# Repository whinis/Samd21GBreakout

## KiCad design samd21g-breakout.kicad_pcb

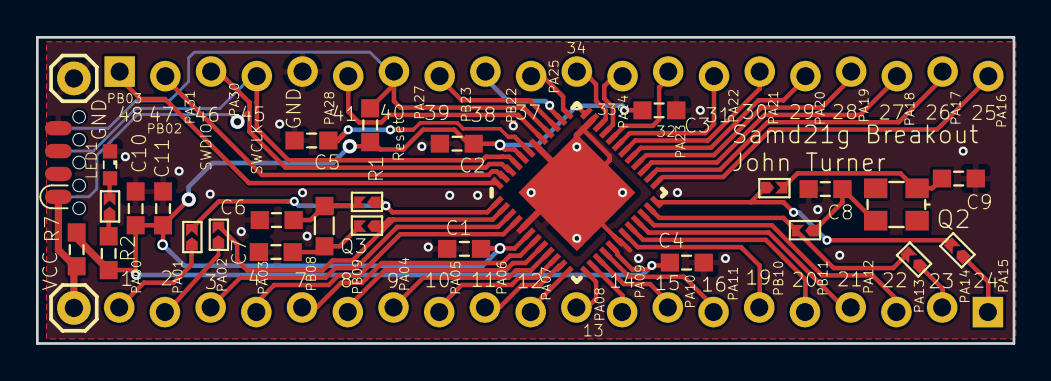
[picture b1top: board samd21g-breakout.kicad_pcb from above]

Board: 2 copper layers, 54.3 x 17.0 mm, 32 parts (0 on the bottom side), 53 nets.

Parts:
C1, C2, C3, C4: 1nf; 0603
C5: 1uf; 0603
C6, C7, C8, C9: CAPACITOR; 0603
C10: 10nf; 0603
C11: 100nf; 0603
J1, J2: CONN_20; PinHeader_1x20_P2.54mm_Vertical_stagger
J3: Conn_02x04_Odd_Even; SOIC_clipProgSmall
J5, J6: CONN_01; 1X01
JP1, JP2, JP3, JP4, JP5, JP6, JP7, JP8, JP9: Jumper_2_Open; SolderJumper-2_P0.6mm_Open_TrianglePad1.0x1.5mm
LED1: LEDSML0603; SML0603
Q2: 48mhz; 3.2X2.5_KX-7
Q3: CRYSTAL3.2X1.5; 3.2X1.5
R1: 10k; 0603
R2, R7: 68; 0603
U$1: ATSAMD21G17A; QFN48

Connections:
/GND: C1.2, C2.2, C3.2, C4.2, C5.2, C6.1, C7.2, C8.1, C9.2, C10.2, C11.2, J2.5, J3.7, J6.1, LED1.C, U$1.5, U$1.18, U$1.35, U$1.42, U$1.EP
/RESET: J2.7, J3.8, R1.1, U$1.40
/SWCLK: J2.4, J3.6, U$1.45
/SWDIO: J2.3, J3.2, U$1.46
/VCC: C1.1, C2.1, C3.1, C4.1, C10.1, C11.1, R1.2, R2.1, R7.2, U$1.6, U$1.17, U$1.36, U$1.44
/VCC_RAW: J3.1, J5.1, R7.1
/VDDCORE: C5.1, U$1.43
unnamed: C6.2, JP5.2, Q3.2
unnamed: C7.1, JP6.2, Q3.1
unnamed: C8.2, JP7.1, Q2.3
unnamed: C9.1, JP8.2, Q2.1
unnamed: J1.1, JP4.1
unnamed: J1.2, JP3.1
unnamed: J1.3, U$1.22
unnamed: J1.4, U$1.21
unnamed: J1.5, U$1.20
unnamed: J1.6, U$1.19
unnamed: J1.7, U$1.16
unnamed: J1.8, U$1.15
unnamed: J1.9, U$1.14
unnamed: J1.10, U$1.13
unnamed: J1.11, U$1.12
unnamed: J1.12, U$1.11
unnamed: J1.13, U$1.10
unnamed: J1.14, U$1.9
unnamed: J1.15, U$1.8
unnamed: J1.16, U$1.7
unnamed: J1.17, U$1.4
unnamed: J1.18, U$1.3
unnamed: J1.19, JP2.1
unnamed: J1.20, JP1.1
unnamed: J2.1, U$1.48
unnamed: J2.2, U$1.47
unnamed: J2.6, U$1.41
unnamed: J2.8, U$1.39
unnamed: J2.9, U$1.38
unnamed: J2.10, U$1.37
unnamed: J2.11, U$1.34
unnamed: J2.12, U$1.33
unnamed: J2.13, U$1.32
unnamed: J2.14, U$1.31
unnamed: J2.15, U$1.30
unnamed: J2.16, U$1.29
unnamed: J2.17, U$1.28
unnamed: J2.18, U$1.27
unnamed: J2.19, U$1.26
unnamed: J2.20, U$1.25
unnamed: JP1.2, JP5.1, U$1.1
unnamed: JP2.2, JP6.1, U$1.2
unnamed: JP3.2, JP7.2, U$1.23
unnamed: JP4.2, JP8.1, U$1.24
unnamed: JP9.1, R2.2
unnamed: JP9.2, LED1.A

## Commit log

2020-06-04 Initial Commit of BreakoutPCB
